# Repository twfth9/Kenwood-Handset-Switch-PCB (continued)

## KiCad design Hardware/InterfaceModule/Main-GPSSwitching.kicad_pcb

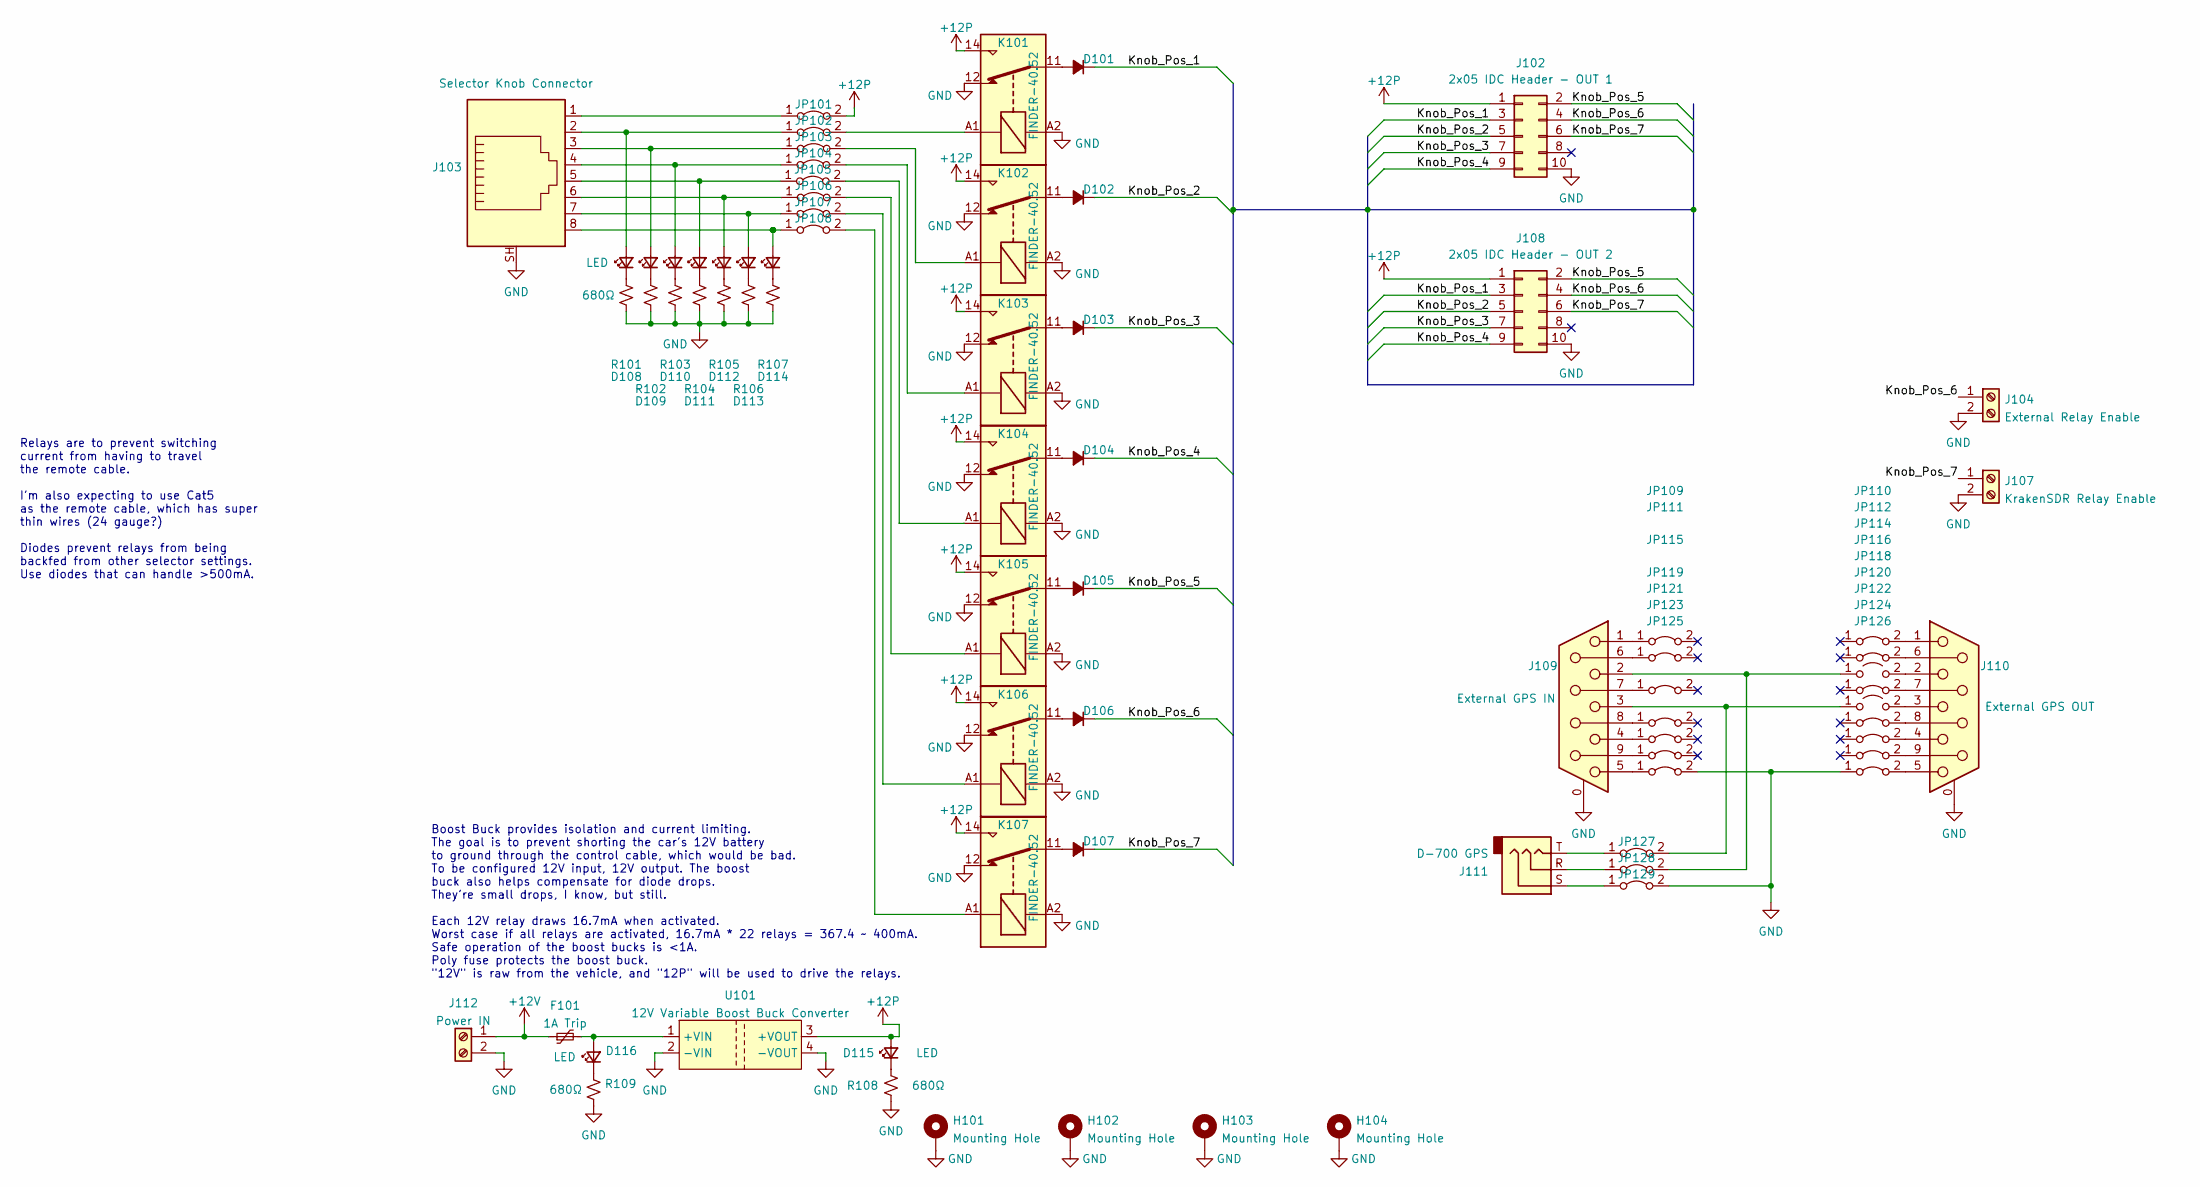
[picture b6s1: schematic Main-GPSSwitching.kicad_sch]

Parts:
D101, D102, D103, D104, D105, D106, D107: D_Small_Filled; D_A-405_P2.54mm_Vertical_AnodeUp
D108, D109, D110, D111, D112, D113, D114, D115, D116: LED; LED_D3.0mm
F101: 1A Trip; Fuse_Bourns_MF-RG300
H101, H102, H103, H104: Mounting Hole; M3_Mounting
J102: 2x05 IDC Header - OUT 1; IDC-Header_2x05_P2.54mm_Vertical
J103: Selector Knob Connector; Mystery_RJ45
J104: External Relay Enable; TerminalBlock_Phoenix_MKDS-1,5-2_1x02_P5.00mm_Horizontal
J107: KrakenSDR Relay Enable; TerminalBlock_Phoenix_MKDS-1,5-2_1x02_P5.00mm_Horizontal
J108: 2x05 IDC Header - OUT 2; IDC-Header_2x05_P2.54mm_Vertical
J109: External GPS IN; DSUB-9_Male_Horizontal_P2.77x2.84mm_EdgePinOffset7.70mm_Hou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
J110: External GPS OUT; DSUB-9_Male_Horizontal_P2.77x2.84mm_EdgePinOffset7.70mm_Hou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
J111: D-700 GPS; Mystery_3.5mm
J112: Power IN; TerminalBlock_Phoenix_MKDS-1,5-2_1x02_P5.00mm_Horizontal
JP101, JP102, JP103, JP104, JP105, JP106, JP107, JP108, JP109, JP110, JP111, JP112, JP115, JP116, JP119, JP120, JP121, JP122, JP123, JP124, JP125, JP126, JP127, JP128, JP129: Jumper_2_Bridged; 1.0mm_Bridge
JP114, JP118: Jumper_2_Bridged; 1.0mm_Bridge_Open
K101, K102, K103, K104, K105, K106, K107: FINDER-40.52; Relay_DPDT_Finder_30.22
R101, R102, R103, R104, R105, R106, R107, R108, R109: 680Ω; R_Axial_DIN0207_L6.3mm_D2.5mm_P2.54mm_Vertical
U101: 12V Variable Boost Buck Converter; BoostBuck

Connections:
+12P: D115.2 (A), J102.1, J108.1, JP101.2 (B), K101.14, K102.14, K103.14, K104.14, K105.14, K106.14, K107.14, U101.3 (+VOUT)
+12V: F101.1, J112.1
/Main & GPS Switching/Knob_Pos_1: D101.1 (K), J102.3, J108.3
/Main & GPS Switching/Knob_Pos_2: D102.1 (K), J102.5, J108.5
/Main & GPS Switching/Knob_Pos_3: D103.1 (K), J102.7, J108.7
/Main & GPS Switching/Knob_Pos_4: D104.1 (K), J102.9, J108.9
/Main & GPS Switching/Knob_Pos_5: D105.1 (K), J102.2, J108.2
/Main & GPS Switching/Knob_Pos_6: D106.1 (K), J102.4, J104.1, J108.4
/Main & GPS Switching/Knob_Pos_7: D107.1 (K), J102.6, J107.1, J108.6
GND: H101.1, H102.1, H103.1, H104.1, J102.10, J103.SH, J104.2, J107.2, J108.10, J109.0 (PAD), J110.0 (PAD), J112.2, JP125.2 (B), JP126.1 (A), JP129.2 (B), K101.12, K101.A2, K102.12, K102.A2, K103.12, K103.A2, K104.12, K104.A2, K105.12, K105.A2, K106.12, K106.A2, K107.12, K107.A2, R101.2, R102.2, R103.2, R104.2, R105.2, R106.2, R107.2, R108.2, R109.2, U101.2 (-VIN), U101.4 (-VOUT)
unnamed: D101.2 (A), K101.11
unnamed: D102.2 (A), K102.11
unnamed: D103.2 (A), K103.11
unnamed: D104.2 (A), K104.11
unnamed: D105.2 (A), K105.11
unnamed: D106.2 (A), K106.11
unnamed: D107.2 (A), K107.11
unnamed: D108.1 (K), R101.1
unnamed: D108.2 (A), J103.2, JP102.1 (A)
unnamed: D109.1 (K), R102.1
unnamed: D109.2 (A), J103.3, JP103.1 (A)
unnamed: D110.1 (K), R103.1
unnamed: D110.2 (A), J103.4, JP104.1 (A)
unnamed: D111.1 (K), R104.1
unnamed: D111.2 (A), J103.5, JP105.1 (A)
unnamed: D112.1 (K), R105.1
unnamed: D112.2 (A), J103.6, JP106.1 (A)
unnamed: D113.1 (K), R106.1
unnamed: D113.2 (A), J103.7, JP107.1 (A)
unnamed: D114.1 (K), R107.1
unnamed: D114.2 (A), J103.8, JP108.1 (A)
unnamed: D115.1 (K), R108.1
unnamed: D116.1 (K), R109.1
unnamed: D116.2 (A), F101.2, U101.1 (+VIN)
unnamed: J103.1, JP101.1 (A)
unnamed: J109.1, JP109.1 (A)
unnamed: J109.2, JP114.1 (A), JP128.2 (B)
unnamed: J109.3, JP118.1 (A), JP127.2 (B)
unnamed: J109.4, JP121.1 (A)
unnamed: J109.5, JP125.1 (A)
unnamed: J109.6, JP111.1 (A)
unnamed: J109.7, JP115.1 (A)
unnamed: J109.8, JP119.1 (A)
unnamed: J109.9, JP123.1 (A)
unnamed: J110.1, JP110.2 (B)
unnamed: J110.2, JP114.2 (B)
unnamed: J110.3, JP118.2 (B)
unnamed: J110.4, JP122.2 (B)
unnamed: J110.5, JP126.2 (B)
unnamed: J110.6, JP112.2 (B)
unnamed: J110.7, JP116.2 (B)
unnamed: J110.8, JP120.2 (B)
unnamed: J110.9, JP124.2 (B)
unnamed: J111.R, JP128.1 (A)
unnamed: J111.S, JP129.1 (A)
unnamed: J111.T, JP127.1 (A)
unnamed: JP102.2 (B), K101.A1
unnamed: JP103.2 (B), K102.A1
unnamed: JP104.2 (B), K103.A1
unnamed: JP105.2 (B), K104.A1
unnamed: JP106.2 (B), K105.A1
unnamed: JP107.2 (B), K106.A1
unnamed: JP108.2 (B), K107.A1

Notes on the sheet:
Relays are to prevent switching current from having to travel the remote cable. I'm also expecting to use Cat5 as the remote cable, which has super thin wires (24 gauge?) Diodes prevent relays from being backfed from other selector settings. Use diodes that can handle >500mA.
Boost Buck provides isolation and current limiting. The goal is to prevent shorting the car's 12V battery to ground through the control cable, which would be bad. To be configured 12V input, 12V output. The boost buck also helps compensate for diode drops. They're small drops, I know, but still. Ea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

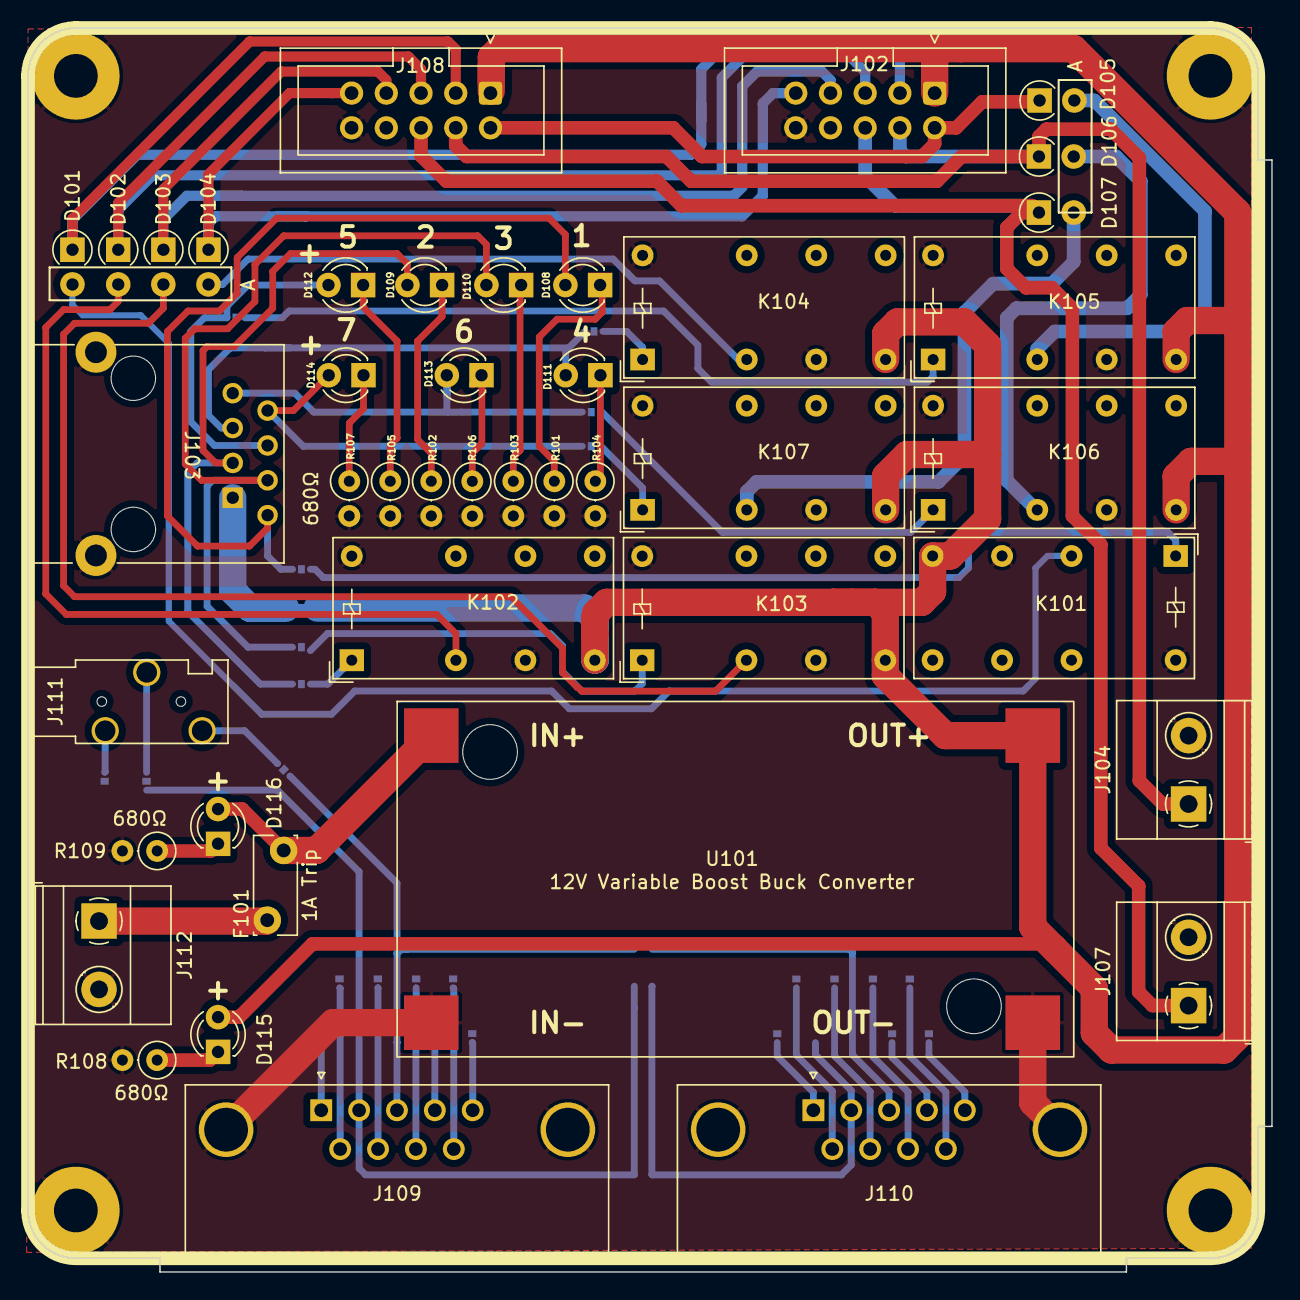
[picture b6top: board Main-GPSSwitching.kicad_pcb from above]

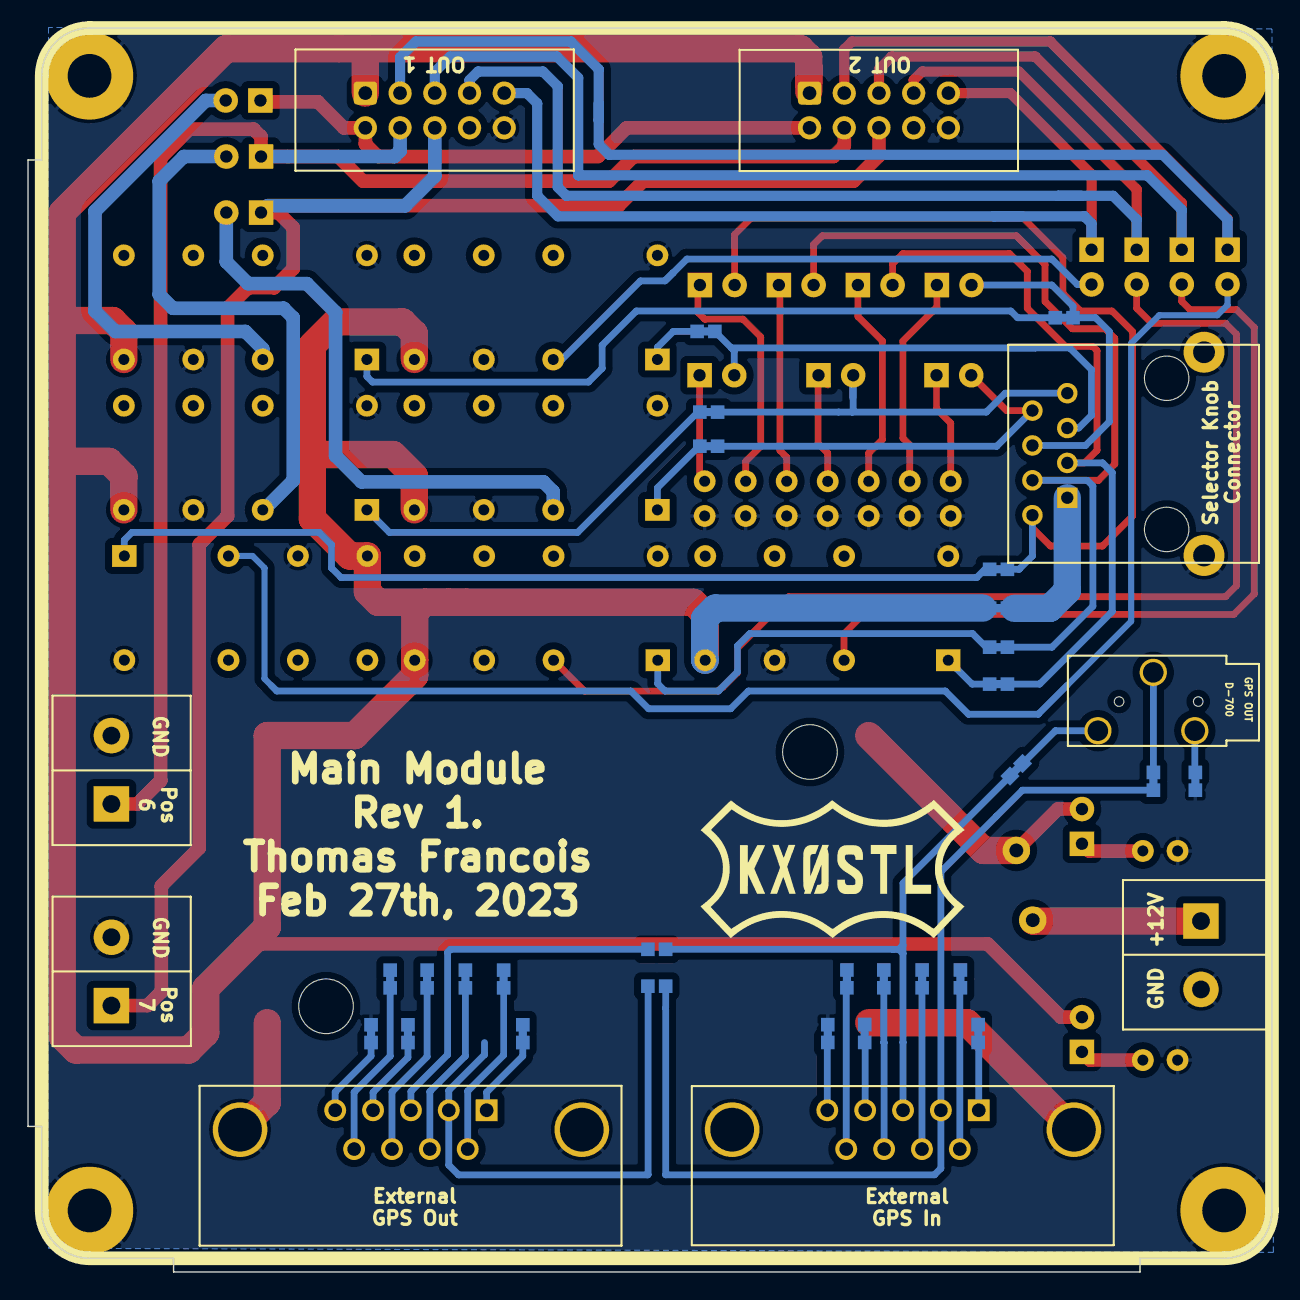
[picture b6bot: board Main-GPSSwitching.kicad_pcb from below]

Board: 2 copper layers, 91.0 x 91.0 mm, 74 parts (27 on the bottom side), 63 nets.

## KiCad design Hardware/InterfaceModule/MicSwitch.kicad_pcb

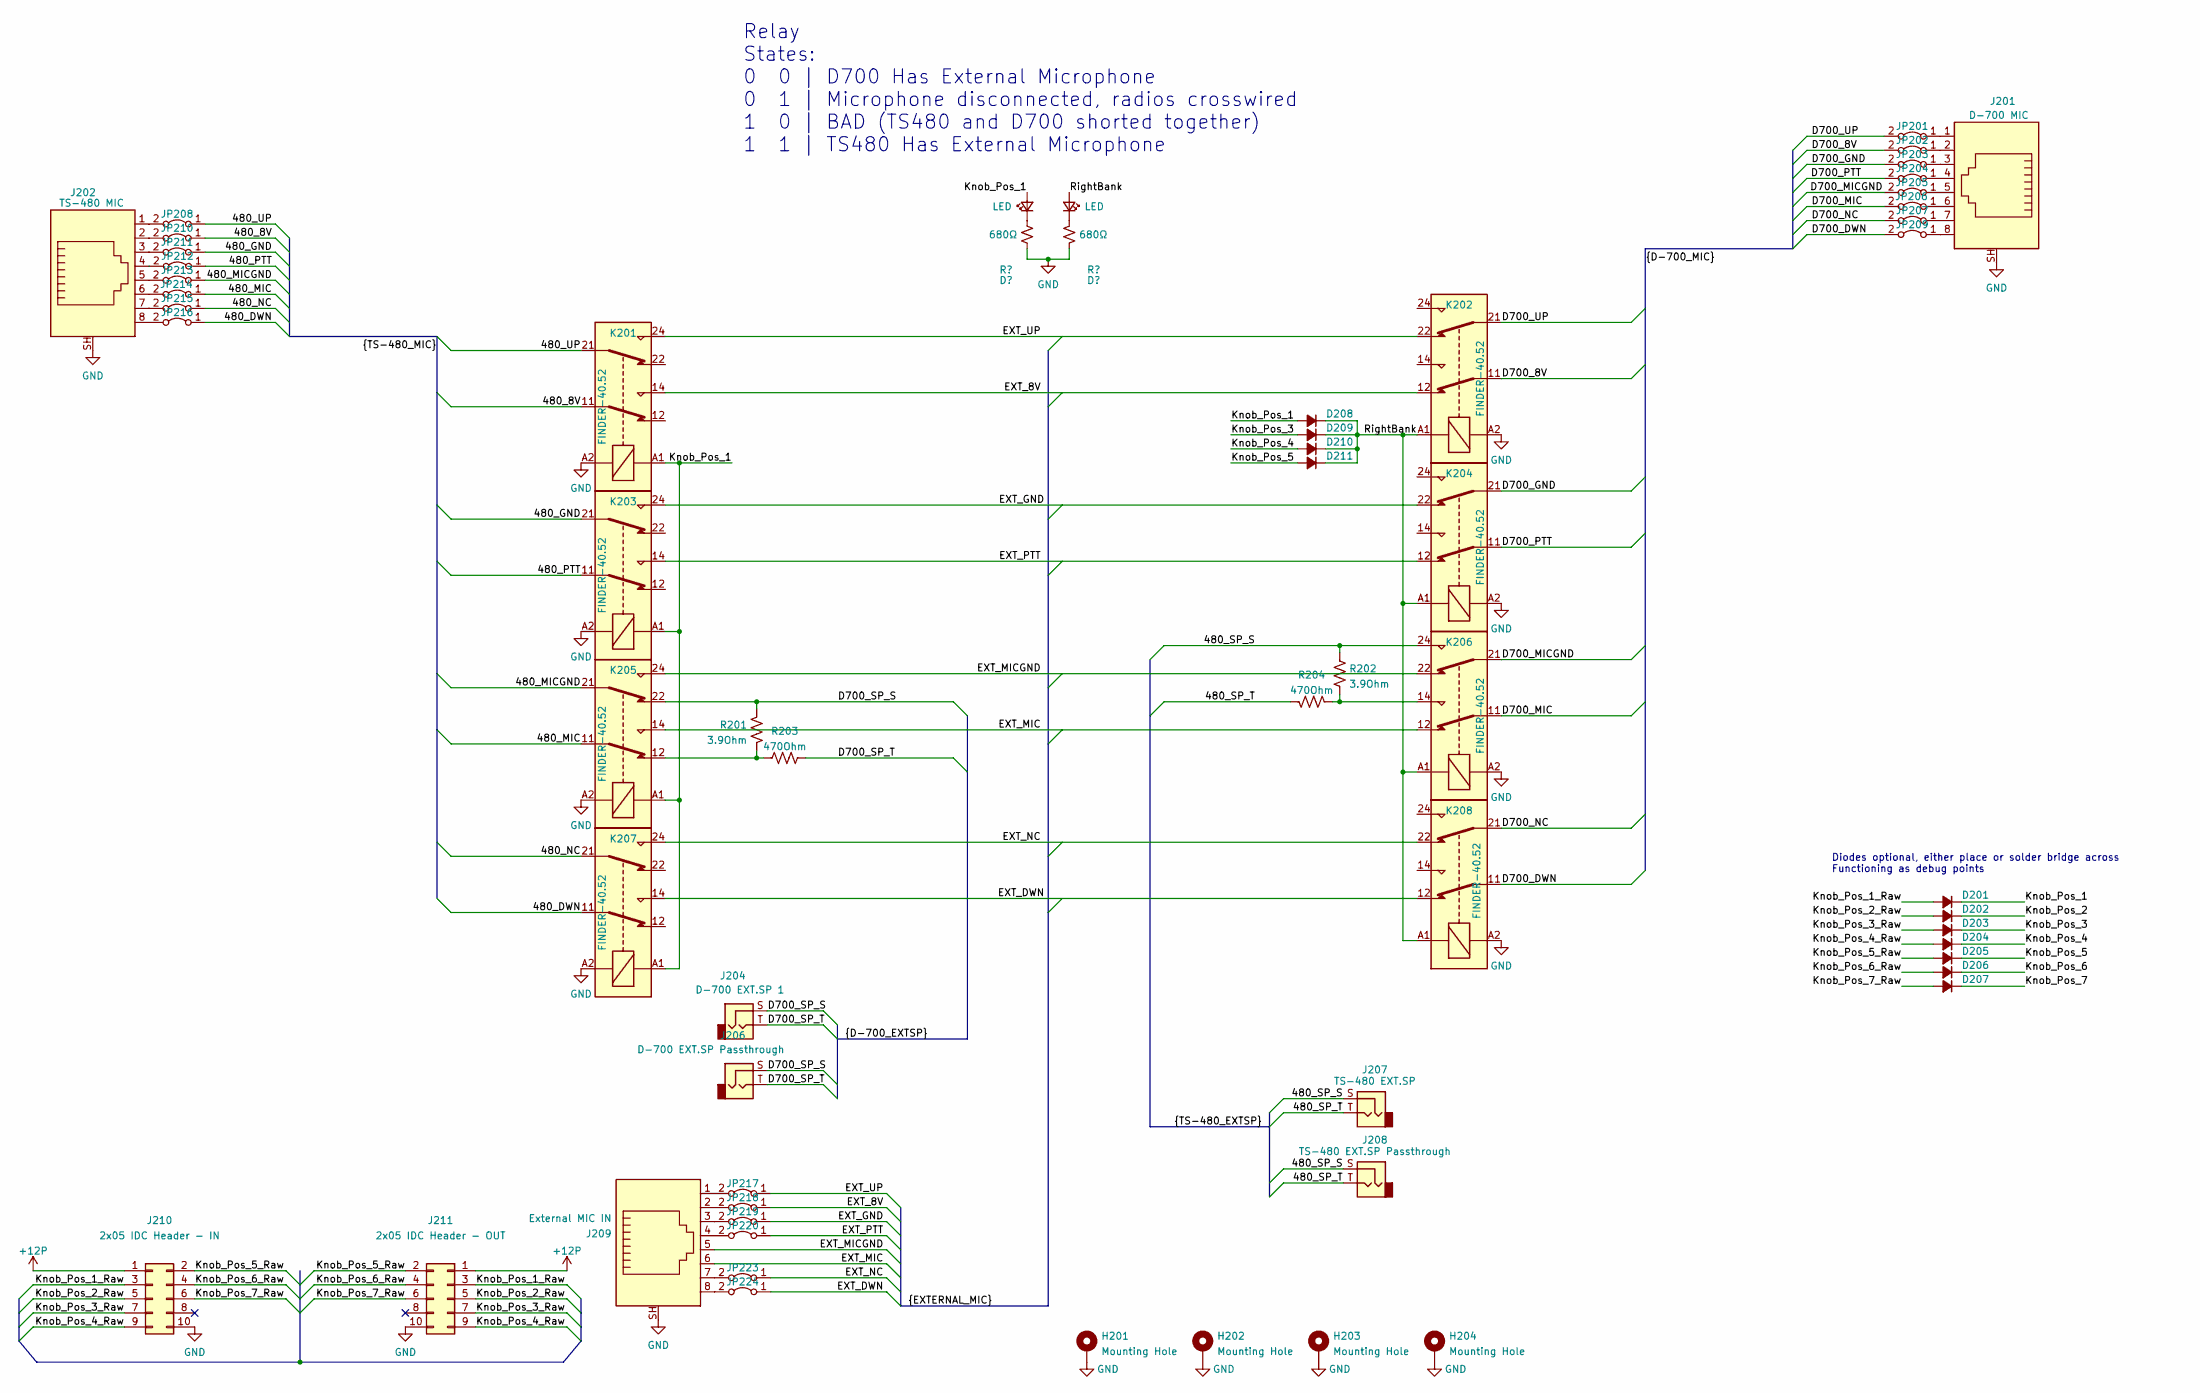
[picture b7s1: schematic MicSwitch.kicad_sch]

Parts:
D201, D202, D203, D204, D205, D206, D207, D208, D209, D210, D211: D_Small_Filled; D_A-405_P2.54mm_Vertical_AnodeUp
H201, H202, H203, H204: Mounting Hole; M3_Mounting
J201: D-700 MIC; Mystery_RJ45
J202: TS-480 MIC; Mystery_RJ45
J204: D-700 EXT.SP 1; Mystery_3.5mm
J206: D-700 EXT.SP Passthrough; Mystery_3.5mm
J207: TS-480 EXT.SP; Mystery_3.5mm
J208: TS-480 EXT.SP Passthrough; Mystery_3.5mm
J209: External MIC IN; Mystery_RJ45
J210: 2x05 IDC Header - IN; IDC-Header_2x05_P2.54mm_Vertical
J211: 2x05 IDC Header - OUT; IDC-Header_2x05_P2.54mm_Vertical
JP201, JP202, JP203, JP204, JP205, JP206, JP207, JP208, JP209, JP210, JP211, JP212, JP213, JP214, JP215, JP216, JP217, JP218, JP219, JP220, JP223, JP224: Jumper_2_Bridged; 1.0mm_Bridge
K201, K202, K203, K204, K205, K206, K207, K208: FINDER-40.52; Relay_DPDT_Finder_30.22
R201, R202: 3.9Ohm; R_Axial_DIN0207_L6.3mm_D2.5mm_P2.54mm_Vertical
R203, R204: 470Ohm; R_Axial_DIN0207_L6.3mm_D2.5mm_P2.54mm_Vertical

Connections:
+12P: J210.1, J211.1
/Microphone Switching/480_8V: JP210.1 (A), K201.11
/Microphone Switching/480_DWN: JP216.1 (A), K207.11
/Microphone Switching/480_GND: JP211.1 (A), K203.21
/Microphone Switching/480_MIC: JP214.1 (A), K205.11
/Microphone Switching/480_MICGND: JP213.1 (A), K205.21
/Microphone Switching/480_NC: JP215.1 (A), K207.21
/Microphone Switching/480_PTT: JP212.1 (A), K203.11
/Microphone Switching/480_SP_S: J207.S, J208.S, K206.24, R202.1
/Microphone Switching/480_SP_T: J207.T, J208.T, R204.1
/Microphone Switching/480_UP: JP208.1 (A), K201.21
/Microphone Switching/D700_8V: JP202.2 (B), K202.11
/Microphone Switching/D700_DWN: JP209.2 (B), K208.11
/Microphone Switching/D700_GND: JP203.2 (B), K204.21
/Microphone Switching/D700_MIC: JP206.2 (B), K206.11
/Microphone Switching/D700_MICGND: JP205.2 (B), K206.21
/Microphone Switching/D700_NC: JP207.2 (B), K208.21
/Microphone Switching/D700_PTT: JP204.2 (B), K204.11
/Microphone Switching/D700_SP_S: J204.S, J206.S, K205.22, R201.1
/Microphone Switching/D700_SP_T: J204.T, J206.T, R203.1
/Microphone Switching/D700_UP: JP201.2 (B), K202.21
/Microphone Switching/EXT_8V: JP218.1 (A), K201.14, K202.12
/Microphone Switching/EXT_DWN: JP224.1 (A), K207.14, K208.12
/Microphone Switching/EXT_GND: JP219.1 (A), K203.24, K204.22
/Microphone Switching/EXT_MIC: J209.6, K205.14, K206.12
/Microphone Switching/EXT_MICGND: J209.5, K205.24, K206.22
/Microphone Switching/EXT_NC: JP223.1 (A), K207.24, K208.22
/Microphone Switching/EXT_PTT: JP220.1 (A), K203.14, K204.12
/Microphone Switching/EXT_UP: JP217.1 (A), K201.24, K202.22
/Microphone Switching/Knob_Pos_1: D201.1 (K), D208.2 (A), K201.A1, K203.A1, K205.A1, K207.A1; also elsewhere on the board
/Microphone Switching/Knob_Pos_1_Raw: D201.2 (A), J210.3, J211.3
/Microphone Switching/Knob_Pos_2: D202.1 (K)
/Microphone Switching/Knob_Pos_2_Raw: D202.2 (A), J210.5, J211.5
/Microphone Switching/Knob_Pos_3: D203.1 (K), D209.2 (A)
/Microphone Switching/Knob_Pos_3_Raw: D203.2 (A), J210.7, J211.7
/Microphone Switching/Knob_Pos_4: D204.1 (K), D210.2 (A)
/Microphone Switching/Knob_Pos_4_Raw: D204.2 (A), J210.9, J211.9
/Microphone Switching/Knob_Pos_5: D205.1 (K), D211.2 (A)
/Microphone Switching/Knob_Pos_5_Raw: D205.2 (A), J210.2, J211.2
/Microphone Switching/Knob_Pos_6: D206.1 (K)
/Microphone Switching/Knob_Pos_6_Raw: D206.2 (A), J210.4, J211.4
/Microphone Switching/Knob_Pos_7: D207.1 (K)
/Microphone Switching/Knob_Pos_7_Raw: D207.2 (A), J210.6, J211.6
/Microphone Switching/RightBank: D208.1 (K), D209.1 (K), D210.1 (K), D211.1 (K), K202.A1, K204.A1, K206.A1, K208.A1; also elsewhere on the board
GND: H201.1, H202.1, H203.1, H204.1, J201.SH, J202.SH, J209.SH, J210.10, J211.10, K201.A2, K202.A2, K203.A2, K204.A2, K205.A2, K206.A2, K207.A2, K208.A2; also elsewhere on the board
unnamed: J201.1, JP201.1 (A)
unnamed: J201.2, JP202.1 (A)
unnamed: J201.3, JP203.1 (A)
unnamed: J201.4, JP204.1 (A)
unnamed: J201.5, JP205.1 (A)
unnamed: J201.6, JP206.1 (A)
unnamed: J201.7, JP207.1 (A)
unnamed: J201.8, JP209.1 (A)
unnamed: J202.1, JP208.2 (B)
unnamed: J202.2, JP210.2 (B)
unnamed: J202.3, JP211.2 (B)
unnamed: J202.4, JP212.2 (B)
unnamed: J202.5, JP213.2 (B)
unnamed: J202.6, JP214.2 (B)
unnamed: J202.7, JP215.2 (B)
unnamed: J202.8, JP216.2 (B)
unnamed: J209.1, JP217.2 (B)
unnamed: J209.2, JP218.2 (B)
unnamed: J209.3, JP219.2 (B)
unnamed: J209.4, JP220.2 (B)
unnamed: J209.7, JP223.2 (B)
unnamed: J209.8, JP224.2 (B)
unnamed: K205.12, R201.2, R203.2
unnamed: K206.14, R202.2, R204.2

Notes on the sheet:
Relay States: 0 0 | D700 Has External Microphone 0 1 | Microphone disconnected, radios crosswired 1 0 | BAD (TS480 and D700 shorted together) 1 1 | TS480 Has External Microphone
Diodes optional, either place or solder bridge across Functioning as debug points

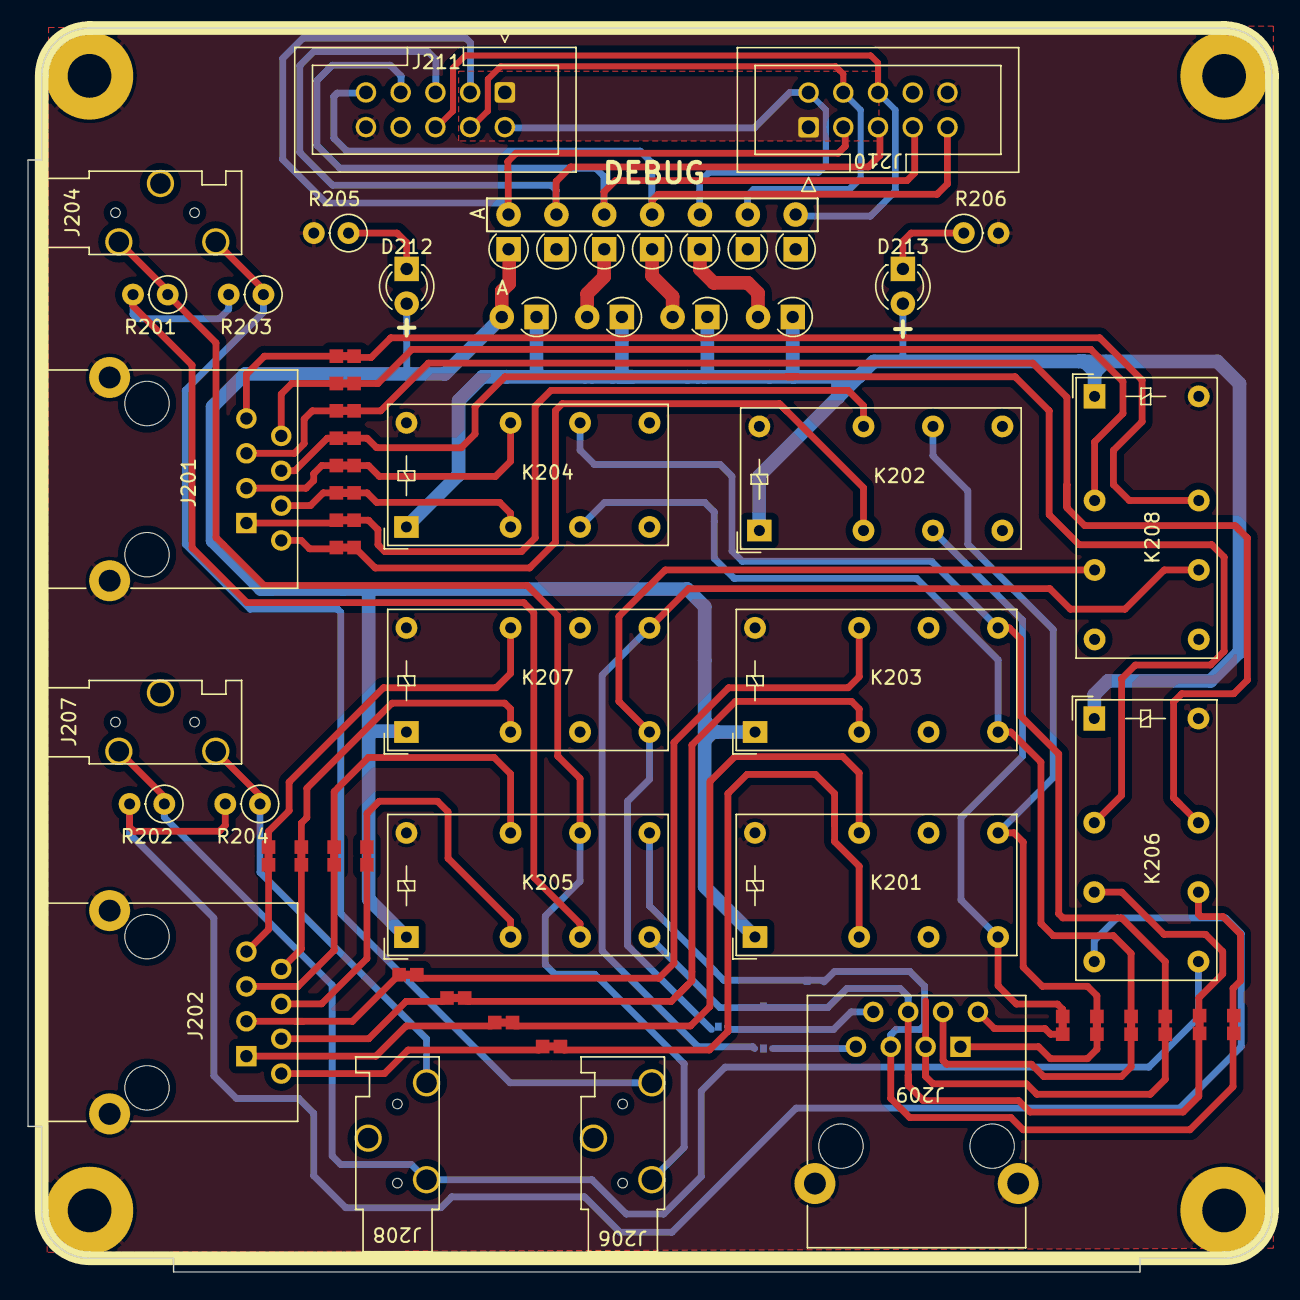
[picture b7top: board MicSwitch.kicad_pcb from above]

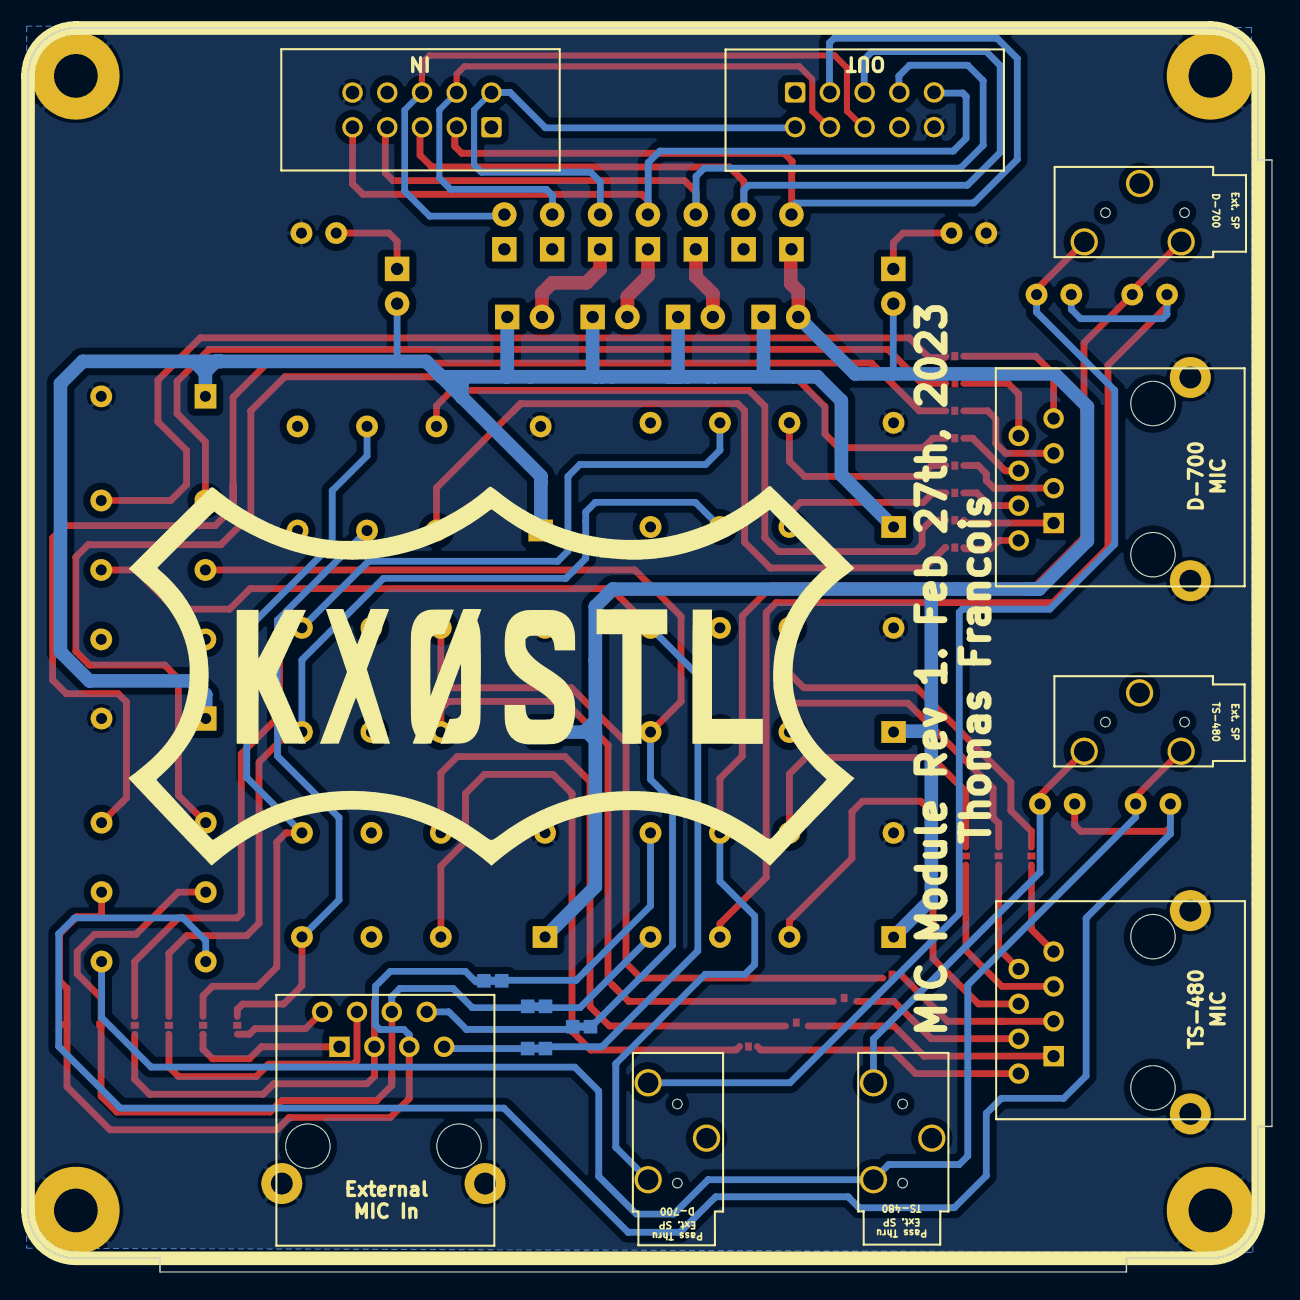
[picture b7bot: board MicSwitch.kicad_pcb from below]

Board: 2 copper layers, 91.0 x 91.0 mm, 66 parts (4 on the bottom side), 68 nets.

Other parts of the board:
D212, D213: LED; LED_D3.0mm
JP225, JP225#2, JP225#3, JP225#4: Jumper_2_Bridged; 1.0mm_Bridge
R205, R206: 680Ω; R_Axial_DIN0207_L6.3mm_D2.5mm_P2.54mm_Vertical

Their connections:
/Microphone Switching/Knob_Pos_1: D212.2 (A); also elsewhere on the board
/Microphone Switching/RightBank: D213.2 (A); also elsewhere on the board
GND: R205.2, R206.2; also elsewhere on the board
unnamed: D212.1 (K), R205.1
unnamed: D213.1 (K), R206.1
